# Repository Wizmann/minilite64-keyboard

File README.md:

# Minilite64 Keyboard

Minilite64 is a 64-key hot-swap keyboard built around a Waveshare
RP2040-Zero.  Its main PCB uses two copper layers; the Vial firmware exposes
four dynamic keymap layers.  The main keyboard PCB and controller carrier are
connected by a 21 mm-wide, 100 mm-long, 20-position 1.0 mm Type-A FFC.  The
design has no per-key lighting.

Assembly is main-board first and controller last.  Lock the main FFC end before
fastening the main PCB, connect the carrier/cover outside the case, then guide
the smooth rear service loop home and install the carrier-cover screws.

## Release contents

- `hardware/keyboard/Minilite64.kicad_pcb` — routed GH60-size main PCB
- `hardware/controller/RP2040_Zero_Carrier.kicad_pcb` — routed 40 x 36 mm carrier
- `hardware/mechanical/Minilite64_plate_fixed.dxf` — corrected plate for PC/FR4 ordering
- `hardware/mechanical/*.stl` and `*.step` — full-size and A1 standing mechanical parts
- `manufacturing/*_gerber.zip` — order-ready PCB packages
- `firmware/vial-qmk/keyboards/minilite64` — Vial-QMK keyboard source
- `firmware/releases/Minilite64_vial.uf2` — locally verified RP2040 firmware
- `docs/DESIGN_AND_REUSE_GUIDE.md` — design history, assembly notes, checks, and reusable lessons

Both PCBs currently report zero DRC violations and zero unconnected items.
The mechanical review reports zero intersections for the checked component,
mounting, controller, stabilizer, cover, and cable envelopes.
The main PCB front silkscreen also carries the complete corrected plate DXF at
1:1 scale for visual Gerber and bare-board inspection.

The checked-in UF2 was built with `arm-none-eabi-gcc 13.2.1`; its SHA-256 is
recorded in `firmware/releases/SHA256SUMS.txt`.

The current mechanical package is **prototype-only** until a real 100 mm FFC
has been installed and repeatedly serviced in a printed case.  Automated solid
checks cannot prove that a flexible cable will settle into the modeled scroll.

## Important fabrication note

Use `hardware/mechanical/Minilite64_plate_fixed.dxf`, not the original
`plate.dxf`.  The original drawing contains an obsolete screw relief merged
into the bottom-row Menu switch opening.  The fixed file removes that conflict
and adds two balanced bottom-row supports, for five round mounts plus two side
mounting slots in total.

See the [design and reuse guide](docs/DESIGN_AND_REUSE_GUIDE.md) before ordering
or assembling the first prototype.

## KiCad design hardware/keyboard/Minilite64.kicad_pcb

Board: 2 copper layers, 134 parts (1 on the bottom side), 83 nets.

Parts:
D1, D2, D3, D4, D5, D6, D7, D8, D9, D10, D11, D12, D13, D14: 1N4148W SOD-123; SOD-123_HandSolder_Horizontal
D15, D16, D17, D18, D19, D20, D21, D22, D23, D24, D25, D26, D27, D28, D29, D30, D31, D32, D33, D34, D35, D36, D37, D38, D39, D40, D41, D42, D43, D44, D45, D46, D47, D48, D49, D50, D51, D52, D53, D54, D55, D56, D57, D58, D59, D60, D61, D62, D63, D64: 1N4148W SOD-123; SOD-123_HandSolder
H1, H2, H3: M2 clearance; MountingHole_2.7mm
H4, H5: M2 clearance; MountingHole_2.4mm
J1: 20P 1.0mm FFC ZIF bottom-contact; FFC_20P_1.0mm_BottomContact_Back
SW1: Kailh MX hotswap / ~ / `; Kailh_MX_Hotswap
SW2: Kailh MX hotswap / ! / 1; Kailh_MX_Hotswap
SW3: Kailh MX hotswap / @ / 2; Kailh_MX_Hotswap
SW4: Kailh MX hotswap / # / 3; Kailh_MX_Hotswap
SW5: Kailh MX hotswap / $ / 4; Kailh_MX_Hotswap
SW6: Kailh MX hotswap / % / 5; Kailh_MX_Hotswap
SW7: Kailh MX hotswap / ^ / 6; Kailh_MX_Hotswap
SW8: Kailh MX hotswap / & / 7; Kailh_MX_Hotswap
SW9: Kailh MX hotswap / * / 8; Kailh_MX_Hotswap
SW10: Kailh MX hotswap / ( / 9; Kailh_MX_Hotswap
SW11: Kailh MX hotswap / ) / 0; Kailh_MX_Hotswap
SW12: Kailh MX hotswap / _ / -; Kailh_MX_Hotswap
SW13: Kailh MX hotswap / + / =; Kailh_MX_Hotswap
SW14: Kailh MX hotswap / Backspace; Kailh_MX_Hotswap
SW15: Kailh MX hotswap / Tab; Kailh_MX_Hotswap
SW16: Kailh MX hotswap / Q; Kailh_MX_Hotswap
SW17: Kailh MX hotswap / W; Kailh_MX_Hotswap
SW18: Kailh MX hotswap / E; Kailh_MX_Hotswap
SW19: Kailh MX hotswap / R; Kailh_MX_Hotswap
SW20: Kailh MX hotswap / T; Kailh_MX_Hotswap
SW21: Kailh MX hotswap / Y; Kailh_MX_Hotswap
SW22: Kailh MX hotswap / U; Kailh_MX_Hotswap
SW23: Kailh MX hotswap / I; Kailh_MX_Hotswap
SW24: Kailh MX hotswap / O; Kailh_MX_Hotswap
SW25: Kailh MX hotswap / P; Kailh_MX_Hotswap
SW26: Kailh MX hotswap / { / [; Kailh_MX_Hotswap
SW27: Kailh MX hotswap / } / ]; Kailh_MX_Hotswap
SW28: Kailh MX hotswap / | / \; Kailh_MX_Hotswap
SW29: Kailh MX hotswap / Caps Lock; Kailh_MX_Hotswap
SW30: Kailh MX hotswap / A; Kailh_MX_Hotswap
SW31: Kailh MX hotswap / S; Kailh_MX_Hotswap
SW32: Kailh MX hotswap / D; Kailh_MX_Hotswap
SW33: Kailh MX hotswap / F; Kailh_MX_Hotswap
SW34: Kailh MX hotswap / G; Kailh_MX_Hotswap
SW35: Kailh MX hotswap / H; Kailh_MX_Hotswap
SW36: Kailh MX hotswap / J; Kailh_MX_Hotswap
SW37: Kailh MX hotswap / K; Kailh_MX_Hotswap
SW38: Kailh MX hotswap / L; Kailh_MX_Hotswap
SW39: Kailh MX hotswap / : / ;; Kailh_MX_Hotswap
SW40: Kailh MX hotswap / " / '; Kailh_MX_Hotswap
SW41: Kailh MX hotswap / Enter; Kailh_MX_Hotswap
SW42, SW53: Kailh MX hotswap / Shift; Kailh_MX_Hotswap
SW43: Kailh MX hotswap / Z; Kailh_MX_Hotswap
SW44: Kailh MX hotswap / X; Kailh_MX_Hotswap
SW45: Kailh MX hotswap / C; Kailh_MX_Hotswap
SW46: Kailh MX hotswap / V; Kailh_MX_Hotswap
SW47: Kailh MX hotswap / B; Kailh_MX_Hotswap
SW48: Kailh MX hotswap / N; Kailh_MX_Hotswap
SW49: Kailh MX hotswap / M; Kailh_MX_Hotswap
SW50: Kailh MX hotswap / < / ,; Kailh_MX_Hotswap
SW51: Kailh MX hotswap / > / .; Kailh_MX_Hotswap
SW52: Kailh MX hotswap / ? / /; Kailh_MX_Hotswap
SW54, SW64: Kailh MX hotswap / Ctrl; Kailh_MX_Hotswap
SW55, SW63: Kailh MX hotswap / Win; Kailh_MX_Hotswap
SW56, SW62: Kailh MX hotswap / Alt; Kailh_MX_Hotswap
SW57: Kailh MX hotswap / Fn1; Kailh_MX_Hotswap
SW58: Kailh MX hotswap /; Kailh_MX_Hotswap
SW59: Kailh MX hotswap / Fn2; Kailh_MX_Hotswap
SW60: Kailh MX hotswap / Menu; Kailh_MX_Hotswap
SW61: Kailh MX hotswap / Fn3; Kailh_MX_Hotswap

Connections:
COL0: J1.1, SW1.1, SW15.1, SW29.1, SW42.1, SW54.1
COL1: J1.2, SW2.1, SW16.1, SW30.1, SW43.1, SW55.1
COL2: J1.3, SW3.1, SW17.1, SW31.1, SW44.1, SW56.1
COL3: J1.4, SW4.1, SW18.1, SW32.1, SW45.1, SW57.1
COL4: J1.5, SW5.1, SW19.1, SW33.1, SW46.1, SW58.1
COL5: J1.6, SW6.1, SW20.1, SW34.1, SW47.1, SW59.1
COL6: J1.7, SW7.1, SW21.1, SW35.1, SW48.1, SW60.1
COL7: J1.8, SW8.1, SW22.1, SW36.1, SW49.1, SW61.1
COL8: J1.9, SW9.1, SW23.1, SW37.1, SW50.1, SW62.1
COL9: J1.10, SW10.1, SW24.1, SW38.1, SW51.1, SW63.1
COL10: J1.11, SW11.1, SW25.1, SW39.1, SW52.1, SW64.1
COL11: J1.12, SW12.1, SW26.1, SW40.1, SW53.1
COL12: J1.13, SW13.1, SW27.1, SW41.1
COL13: J1.14, SW14.1, SW28.1
KEY1_D: D1.1, SW1.2
KEY2_D: D2.1, SW2.2
KEY3_D: D3.1, SW3.2
KEY4_D: D4.1, SW4.2
KEY5_D: D5.1, SW5.2
KEY6_D: D6.1, SW6.2
KEY7_D: D7.1, SW7.2
KEY8_D: D8.1, SW8.2
KEY9_D: D9.1, SW9.2
KEY10_D: D10.1, SW10.2
KEY11_D: D11.1, SW11.2
KEY12_D: D12.1, SW12.2
KEY13_D: D13.1, SW13.2
KEY14_D: D14.1, SW14.2
KEY15_D: D15.1, SW15.2
KEY16_D: D16.1, SW16.2
KEY17_D: D17.1, SW17.2
KEY18_D: D18.1, SW18.2
KEY19_D: D19.1, SW19.2
KEY20_D: D20.1, SW20.2
KEY21_D: D21.1, SW21.2
KEY22_D: D22.1, SW22.2
KEY23_D: D23.1, SW23.2
KEY24_D: D24.1, SW24.2
KEY25_D: D25.1, SW25.2
KEY26_D: D26.1, SW26.2
KEY27_D: D27.1, SW27.2
KEY28_D: D28.1, SW28.2
KEY29_D: D29.1, SW29.2
KEY30_D: D30.1, SW30.2
KEY31_D: D31.1, SW31.2
KEY32_D: D32.1, SW32.2
KEY33_D: D33.1, SW33.2
KEY34_D: D34.1, SW34.2
KEY35_D: D35.1, SW35.2
KEY36_D: D36.1, SW36.2
KEY37_D: D37.1, SW37.2
KEY38_D: D38.1, SW38.2
KEY39_D: D39.1, SW39.2
KEY40_D: D40.1, SW40.2
KEY41_D: D41.1, SW41.2
KEY42_D: D42.1, SW42.2
KEY43_D: D43.1, SW43.2
KEY44_D: D44.1, SW44.2
KEY45_D: D45.1, SW45.2
KEY46_D: D46.1, SW46.2
KEY47_D: D47.1, SW47.2
KEY48_D: D48.1, SW48.2
KEY49_D: D49.1, SW49.2
KEY50_D: D50.1, SW50.2
KEY51_D: D51.1, SW51.2
KEY52_D: D52.1, SW52.2
KEY53_D: D53.1, SW53.2
KEY54_D: D54.1, SW54.2
KEY55_D: D55.1, SW55.2
KEY56_D: D56.1, SW56.2
KEY57_D: D57.1, SW57.2
KEY58_D: D58.1, SW58.2
KEY59_D: D59.1, SW59.2
KEY60_D: D60.1, SW60.2
KEY61_D: D61.1, SW61.2
KEY62_D: D62.1, SW62.2
KEY63_D: D63.1, SW63.2
KEY64_D: D64.1, SW64.2
ROW0: D1.2, D2.2, D3.2, D4.2, D5.2, D6.2, D7.2, D8.2, D9.2, D10.2, D11.2, D12.2, D13.2, D14.2, J1.15
ROW1: D15.2, D16.2, D17.2, D18.2, D19.2, D20.2, D21.2, D22.2, D23.2, D24.2, D25.2, D26.2, D27.2, D28.2, J1.16
ROW2: D29.2, D30.2, D31.2, D32.2, D33.2, D34.2, D35.2, D36.2, D37.2, D38.2, D39.2, D40.2, D41.2, J1.17
ROW3: D42.2, D43.2, D44.2, D45.2, D46.2, D47.2, D48.2, D49.2, D50.2, D51.2, D52.2, D53.2, J1.18
ROW4: D54.2, D55.2, D56.2, D57.2, D58.2, D59.2, D60.2, D61.2, D62.2, D63.2, D64.2, J1.19

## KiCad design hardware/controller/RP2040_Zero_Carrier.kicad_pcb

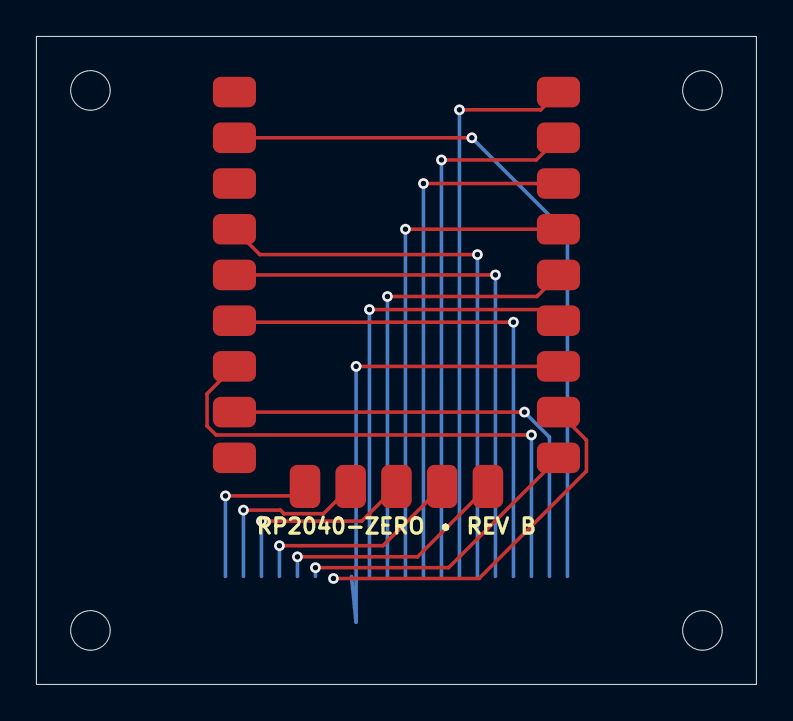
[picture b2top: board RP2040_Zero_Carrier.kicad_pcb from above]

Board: 2 copper layers, 40.0 x 36.0 mm, 6 parts (1 on the bottom side), 20 nets.

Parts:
H1, H2, H3, H4: M2.5 clearance; MountingHole_2.2mm
J1: 20P 1.0mm FFC ZIF bottom-contact; FFC_20P_1.0mm_BottomContact_Back
U1: Waveshare RP2040-Zero; Waveshare_RP2040_Zero_Castellated

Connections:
COL0: J1.1, U1.GP13
COL1: J1.2, U1.GP12
COL2: J1.3, U1.GP11
COL3: J1.4, U1.GP10
COL4: J1.5, U1.GP9
COL5: J1.6, U1.GP8
COL6: J1.7, U1.GP7
COL7: J1.8, U1.GP6
COL8: J1.9, U1.GP5
COL9: J1.10, U1.GP4
COL10: J1.11, U1.GP3
COL11: J1.12, U1.GP2
COL12: J1.13, U1.GP1
COL13: J1.14, U1.GP0
GND: J1.20, U1.GND
ROW0: J1.15, U1.GP29
ROW1: J1.16, U1.GP28
ROW2: J1.17, U1.GP27
ROW3: J1.18, U1.GP26
ROW4: J1.19, U1.GP15
